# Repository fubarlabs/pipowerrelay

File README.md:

# pipowerrelay
Raspberry Pi Power Relay Board

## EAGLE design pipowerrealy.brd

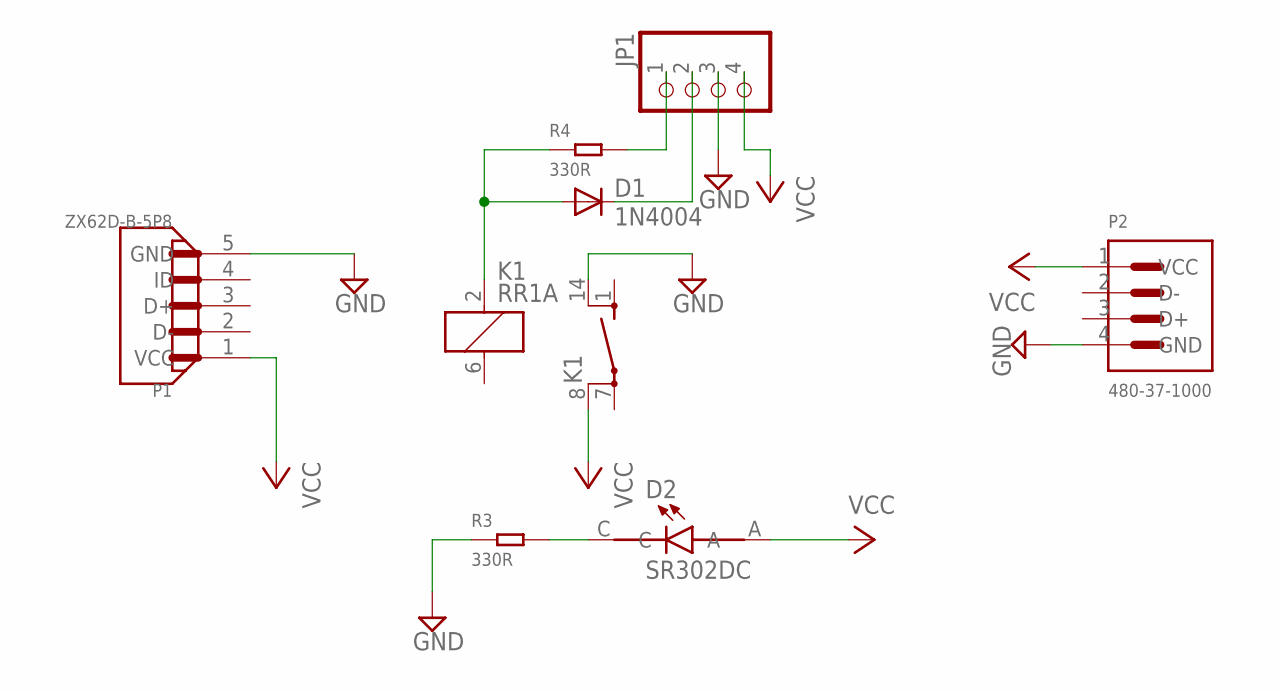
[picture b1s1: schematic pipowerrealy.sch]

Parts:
D1: 1N4004; DO41-10
D2: SR302DC; LED_SR302DC
JP1: PINHD-1X4; 1X04
K1: RR1A
P1: ZX62D-B-5P8; HRS_ZX62D-B-5P8
P2: 480-37-1000; MOLEX_480-37-1000
R3, R4: 330R; PR-D2.3XL6.5MM

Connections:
GND: JP1.3, K1.14 (S), P1.5 (GND), P2.4 (GND), R3.1
unnamed: D2.C, R3.2
unnamed: D1.C, JP1.2
unnamed: JP1.1, R4.2
unnamed: D1.A, K1.2 (1), R4.1
VCC: D2.A, JP1.4, K1.8, P1.1 (VCC), P2.1 (VCC)

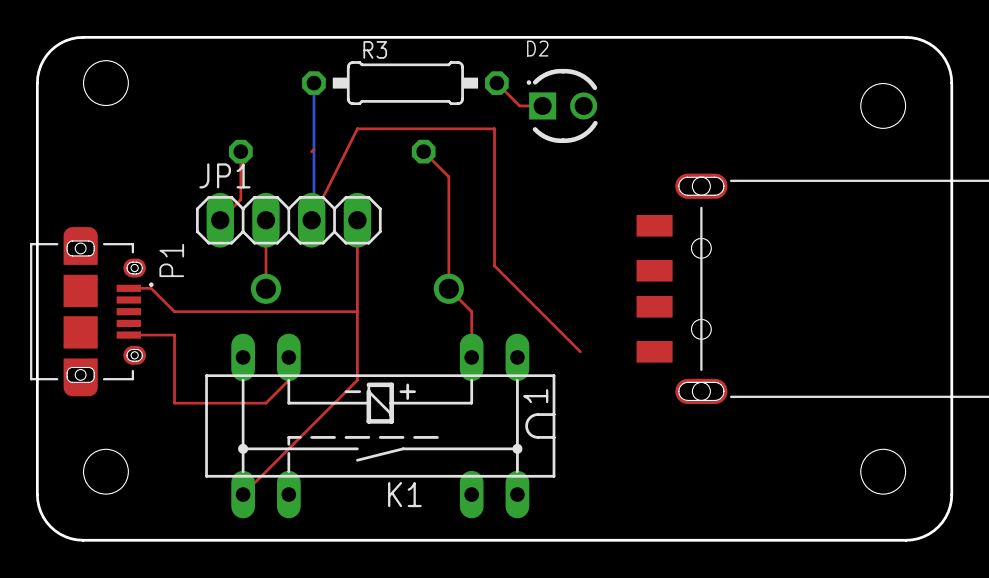
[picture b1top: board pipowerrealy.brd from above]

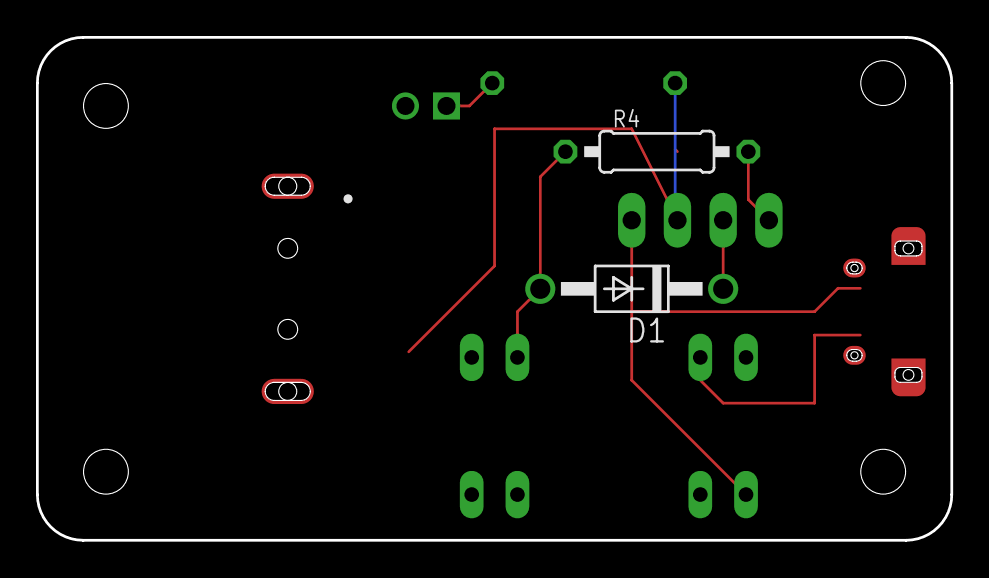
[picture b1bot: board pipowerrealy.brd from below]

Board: 2 copper layers, 50.8 x 27.9 mm, 8 parts (2 on the bottom side), 6 nets.

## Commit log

2018-03-10 added the Eagle files
2018-03-10 Added libraries used in project
2018-03-10 Shrank board. Made a problem for Vccin vs vccout.
